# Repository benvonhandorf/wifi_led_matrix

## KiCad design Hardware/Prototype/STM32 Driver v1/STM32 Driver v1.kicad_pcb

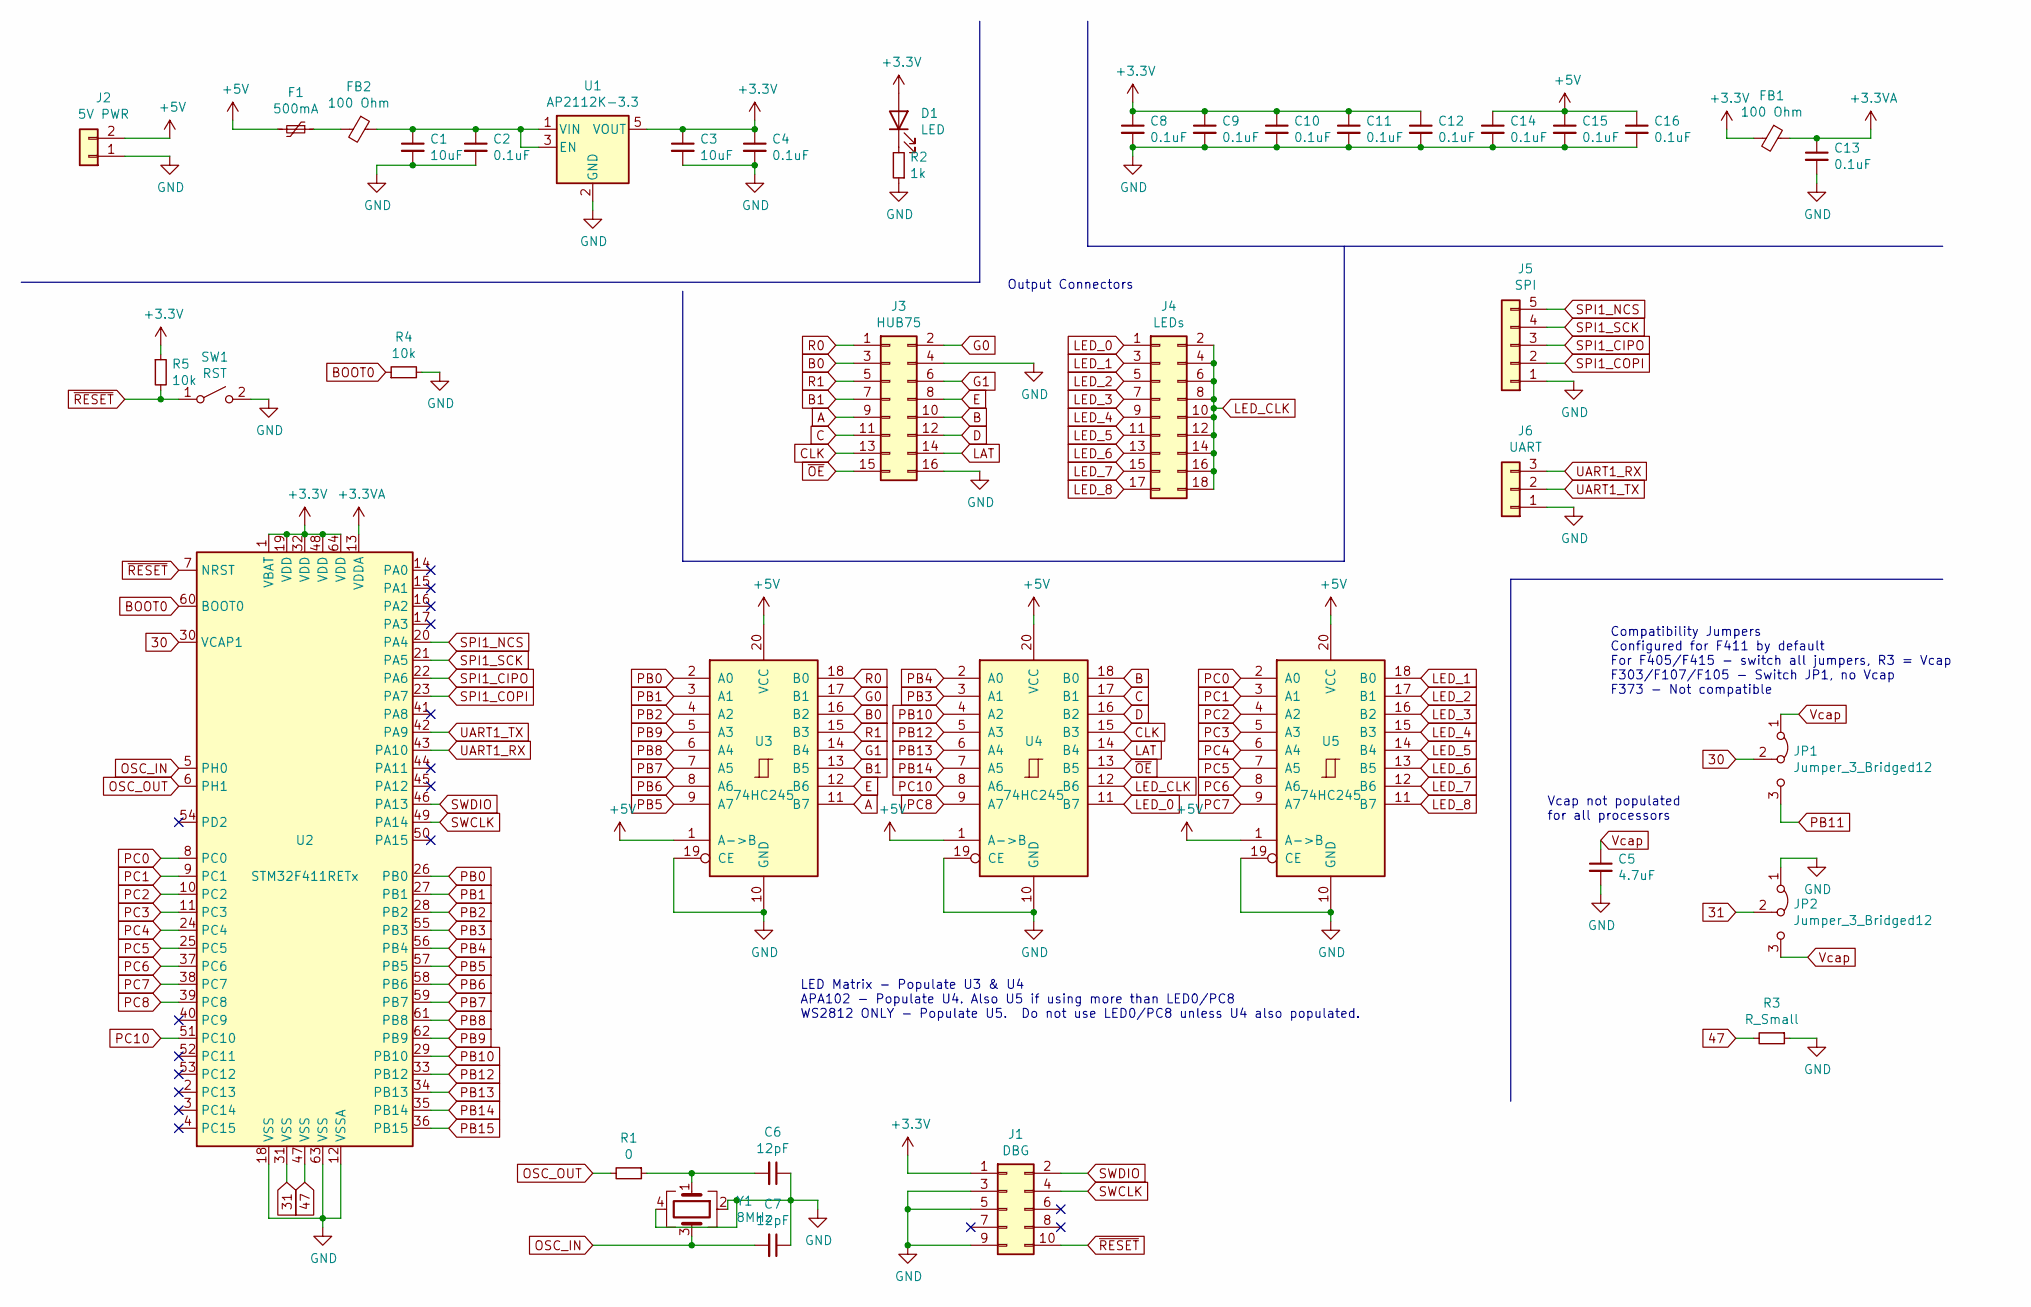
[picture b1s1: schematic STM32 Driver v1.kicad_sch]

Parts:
C1, C3: 10uF; C_0805_2012Metric
C2, C4, C8, C9, C10, C11, C12, C13, C14, C15, C16: 0.1uF; C_0603_1608Metric
C5: 4.7uF; C_0805_2012Metric
C6, C7: 12pF; C_0805_2012Metric
D1: LED; LED_0805_2012Metric
F1: 500mA; Fuse_1210_3225Metric
FB1, FB2: 100 Ohm; L_0805_2012Metric
J1: DBG; Cortex_Debug_PinSocket_2x05_P1.27mm_Vertical_SMD
J2: 5V PWR; TerminalBlock_Phoenix_MKDS-1,5-2-5.08_1x02_P5.08mm_Horizont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
J3: HUB75; IDC-Header_2x08_P2.54mm_Vertical
J4: LEDs; PinHeader_2x09_P2.54mm_Horizontal
J5: SPI; PinHeader_1x05_P2.54mm_Vertical
J6: UART; PinHeader_1x03_P2.54mm_Vertical
JP1, JP2: Jumper_3_Bridged12; SolderJumper-3_P1.3mm_Bridged12_Pad1.0x1.5mm
R1: 0; R_0603_1608Metric
R2: 1k; R_0805_2012Metric
R3: R_Small; R_0805_2012Metric_Pad1.15x1.40mm_HandSolder
R4, R5: 10k; R_0805_2012Metric
SW1: RST; Tac_SMD_6.4mm_Side_SPST_NO
U1: AP2112K-3.3; SOT-23-5
U2: STM32F411RETx; LQFP-64_10x10mm_P0.5mm
U3, U4, U5: 74HC245; TSSOP-20_4.4x6.5mm_P0.65mm
Y1: 8MHz; Crystal_SMD_5032-4Pin_5.0x3.2mm

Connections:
30: JP1.2 (C), U2.30 (VCAP1)
31: JP2.2 (C), U2.31 (VSS)
47: R3.2, U2.47 (VSS)
+3.3VA: C13.1, FB1.1, U2.13 (VDDA)
+5V: C14.1, C15.1, C16.1, F1.2, J2.2, U3.1 (A->B), U3.20 (VCC), U4.1 (A->B), U4.20 (VCC), U5.1 (A->B), U5.20 (VCC)
A: J3.9, U3.11 (B7)
B: J3.10, U4.18 (B0)
B0: J3.3, U3.16 (B2)
B1: J3.7, U3.13 (B5)
BOOT0: R4.1, U2.60 (BOOT0)
C: J3.11, U4.17 (B1)
CLK: J3.13, U4.15 (B3)
D: J3.12, U4.16 (B2)
E: J3.8, U3.12 (B6)
G0: J3.2, U3.17 (B1)
G1: J3.6, U3.14 (B4)
GND: C1.2, C2.2, C3.2, C4.2, C5.2, C6.1, C7.1, C8.2, C9.2, C10.2, C11.2, C12.2, C13.2, C14.2, C15.2, C16.2, J1.3, J1.5, J1.9, J2.1, J3.4, J3.16, J5.1, J6.1, JP2.1 (A), R2.1, R3.1, R4.2, SW1.2 (B), U1.2 (GND), U2.12 (VSSA), U2.18 (VSS), U2.63 (VSS), U3.10 (GND), U3.19 (CE), U4.10 (GND), U4.19 (CE), U5.10 (GND), U5.19 (CE), Y1.2, Y1.4
LAT: J3.14, U4.14 (B4)
LED_0: J4.1, U4.11 (B7)
LED_1: J4.3, U5.18 (B0)
LED_2: J4.5, U5.17 (B1)
LED_3: J4.7, U5.16 (B2)
LED_4: J4.9, U5.15 (B3)
LED_5: J4.11, U5.14 (B4)
LED_6: J4.13, U5.13 (B5)
LED_7: J4.15, U5.12 (B6)
LED_8: J4.17, U5.11 (B7)
LED_CLK: J4.2, J4.4, J4.6, J4.8, J4.10, J4.12, J4.14, J4.16, J4.18, U4.12 (B6)
unnamed: C1.1, C2.1, FB2.1, U1.1 (VIN), U1.3 (EN)
unnamed: C6.2, R1.1, Y1.1
unnamed: D1.1 (K), R2.2
unnamed: F1.1, FB2.2
OSC_IN: C7.2, U2.5 (PH0), Y1.3
OSC_OUT: R1.2, U2.6 (PH1)
PB0: U2.26 (PB0), U3.2 (A0)
PB1: U2.27 (PB1), U3.3 (A1)
PB2: U2.28 (PB2), U3.4 (A2)
PB3: U2.55 (PB3), U4.3 (A1)
PB4: U2.56 (PB4), U4.2 (A0)
PB5: U2.57 (PB5), U3.9 (A7)
PB6: U2.58 (PB6), U3.8 (A6)
PB7: U2.59 (PB7), U3.7 (A5)
PB8: U2.61 (PB8), U3.6 (A4)
PB9: U2.62 (PB9), U3.5 (A3)
PB10: U2.29 (PB10), U4.4 (A2)
PB11: JP1.3 (B)
PB12: U2.33 (PB12), U4.5 (A3)
PB13: U2.34 (PB13), U4.6 (A4)
PB14: U2.35 (PB14), U4.7 (A5)
PB15: U2.36 (PB15)
PC0: U2.8 (PC0), U5.2 (A0)
PC1: U2.9 (PC1), U5.3 (A1)
PC2: U2.10 (PC2), U5.4 (A2)
PC3: U2.11 (PC3), U5.5 (A3)
PC4: U2.24 (PC4), U5.6 (A4)
PC5: U2.25 (PC5), U5.7 (A5)
PC6: U2.37 (PC6), U5.8 (A6)
PC7: U2.38 (PC7), U5.9 (A7)
PC8: U2.39 (PC8), U4.9 (A7)
PC10: U2.51 (PC10), U4.8 (A6)
R0: J3.1, U3.18 (B0)
R1: J3.5, U3.15 (B3)
SPI1_CIPO: J5.3, U2.22 (PA6)
SPI1_COPI: J5.2, U2.23 (PA7)
SPI1_NCS: J5.5, U2.20 (PA4)
SPI1_SCK: J5.4, U2.21 (PA5)
SWCLK: J1.4, U2.49 (PA14)
SWDIO: J1.2, U2.46 (PA13)
UART1_RX: J6.3, U2.43 (PA10)
UART1_TX: J6.2, U2.42 (PA9)
Vcap: C5.1, JP1.1 (A), JP2.3 (B)
~OE: J3.15, U4.13 (B5)
~RESET: J1.10, R5.2, SW1.1 (A), U2.7 (NRST)

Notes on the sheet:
Vcap not populated for all processors
Output Connectors
LED Matrix - Populate U3 & U4 APA102 - Populate U4. Also U5 if using more than LED0/PC8 WS2812 ONLY - Populate U5. Do not use LED0/PC8 unless U4 also populated.
Compatibility Jumpers Configured for F411 by default For F405/F415 - switch all jumpers, R3 = Vcap F303/F107/F105 - Switch JP1, no Vcap F373 - Not compatible

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
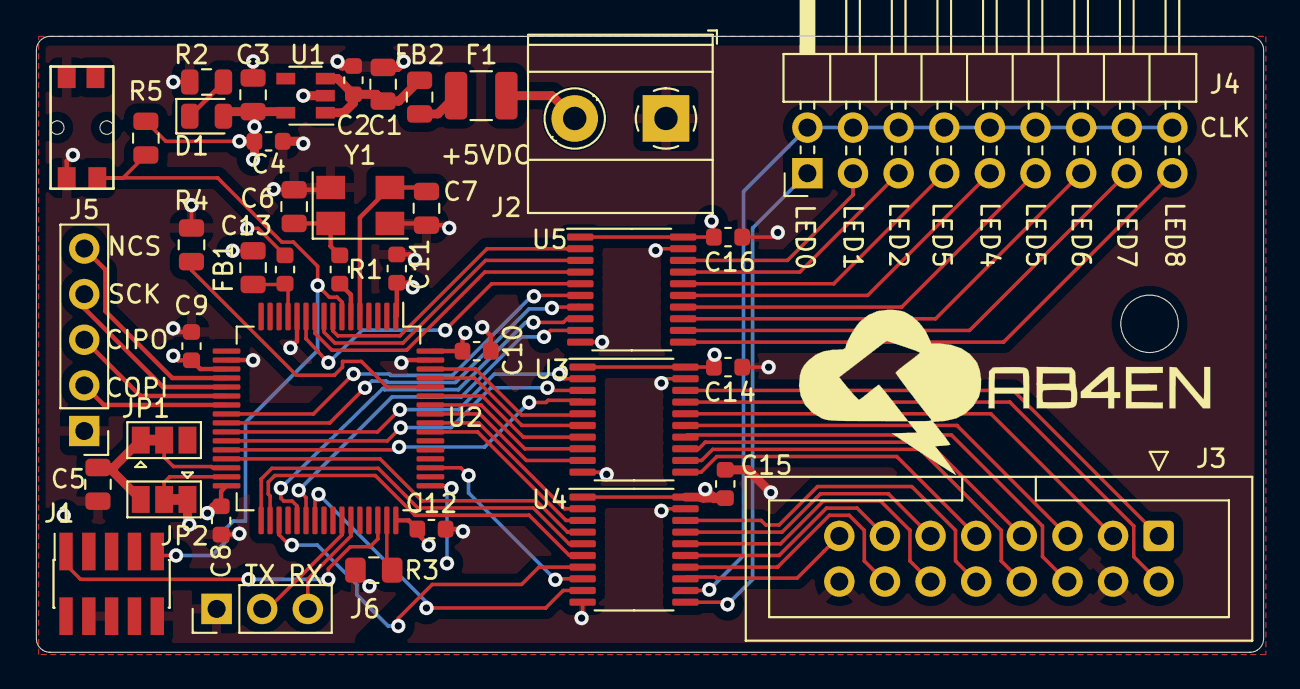
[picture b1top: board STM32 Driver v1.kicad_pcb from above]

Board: 4 copper layers, 68.3 x 34.3 mm, 40 parts (0 on the bottom side), 72 nets.

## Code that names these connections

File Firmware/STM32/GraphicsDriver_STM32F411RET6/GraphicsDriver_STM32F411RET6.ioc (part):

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Mcu.Name=STM32F411R(C-E)Tx
Mcu.Package=LQFP64
Mcu.UserName=STM32F411RETx
PA10.Mode=Asynchronous
PA10.Signal=USART1_RX
PA13.Mode=Serial_Wire
PA13.Signal=SYS_JTMS-SWDIO
PA14.Mode=Serial_Wire
PA14.Signal=SYS_JTCK-SWCLK
PA4.GPIOParameters=GPIO_PuPd,GPIO_Label,GPIO_ModeDefaultEXTI
PA4.GPIO_Label=SPI1_NCS
PA4.GPIO_ModeDefaultEXTI=GPIO_MODE_IT_RISING
PA4.GPIO_PuPd=GPIO_PULLUP
PA4.Signal=GPXTI4
PA5.Mode=Full_Duplex_Slave
PA5.Signal=SPI1_SCK
PA6.Mode=Full_Duplex_Slave
PA6.Signal=SPI1_MISO
PA7.Mode=Full_Duplex_Slave
PA7.Signal=SPI1_MOSI
PA9.Mode=Asynchronous
PA9.Signal=USART1_TX
PB0.GPIOParameters=GPIO_Label
PB0.GPIO_Label=Matrix_R0
PB0.Signal=GPIO_Output
PB1.GPIOParameters=GPIO_Label
PB1.GPIO_Label=Matrix_G0
PB1.Signal=GPIO_Output
PB10.GPIOParameters=GPIO_Label
PB10.GPIO_Label=Matrix_D
PB10.Signal=GPIO_Output
PB12.GPIOParameters=GPIO_Label
PB12.GPIO_Label=Matrix_CLK
PB12.Signal=GPIO_Output
PB13.GPIOParameters=GPIO_Label
PB13.GPIO_Label=Matrix_LAT
PB13.Signal=GPIO_Output
PB14.GPIOParameters=GPIO_Label
PB14.GPIO_Label=Matrix_OE
PB14.Signal=GPIO_Output
PB2.GPIOParameters=GPIO_Label
PB2.GPIO_Label=Matrix_B0
PB2.Signal=GPIO_Output
PB3.GPIOParameters=GPIO_Label
PB3.GPIO_Label=Matrix_C
PB3.Signal=GPIO_Output
PB4.GPIOParameters=GPIO_Label
PB4.GPIO_Label=Matrix_B
PB4.Signal=GPIO_Output
PB5.GPIOParameters=GPIO_Label
PB5.GPIO_Label=Matrix_A
PB5.Signal=GPIO_Output
PB6.GPIOParameters=GPIO_Label
PB6.GPIO_Label=Matrix_E
PB6.Signal=GPIO_Output
PB7.GPIOParameters=GPIO_Label
PB7.GPIO_Label=Matrix_B1
PB7.Signal=GPIO_Output
PB8.GPIOParameters=GPIO_Label
PB8.GPIO_Label=Matrix_G1
PB8.Signal=GPIO_Output
PB9.GPIOParameters=GPIO_Label
PB9.GPIO_Label=Matrix_R1
PB9.Signal=GPIO_Output
PC0.GPIOParameters=GPIO_Label
PC0.GPIO_Label=LED_1
PC0.Signal=GPIO_Output
PC1.GPIOParameters=GPIO_Label
PC1.GPIO_Label=LED_2
PC1.Signal=GPIO_Output
PC10.GPIOParameters=GPIO_Label
PC10.GPIO_Label=LED_CLK
PC10.Signal=GPIO_Output
PC2.GPIOParameters=GPIO_Label
PC2.GPIO_Label=LED_3
PC2.Signal=GPIO_Output
PC3.GPIOParameters=GPIO_Label
PC3.GPIO_Label=LED_4
PC3.Signal=GPIO_Output
PC4.GPIOParameters=GPIO_Label
PC4.GPIO_Label=LED_5
PC4.Signal=GPIO_Output
PC5.GPIOParameters=GPIO_Label
PC5.GPIO_Label=LED_6
PC5.Signal=GPIO_Output
PC6.GPIOParameters=GPIO_Label
PC6.GPIO_Label=LED_7
PC6.Signal=GPIO_Output
PC7.GPIOParameters=GPIO_Label
PC7.GPIO_Label=LED_8
PC7.Signal=GPIO_Output
PC8.GPIOParameters=GPIO_Label
PC8.GPIO_Label=LED_0
PC8.Signal=GPIO_Output
PH0\ -\ OSC_IN.Mode=HSE-External-Oscillator
PH0\ -\ OSC_IN.Signal=RCC_OSC_IN
PH1\ -\ OSC_OUT.Mode=HSE-External-Oscillator
PH1\ -\ OSC_OUT.Signal=RCC_OSC_OUT
RCC.HSE_VALUE=8000000
RCC.SYSCLKFreq_VALUE=100000000
RCC.SYSCLKSource=RCC_SYSCLKSOURCE_PLLCLK
board=custom

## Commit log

2020-09-26 Basic gif-frames library working
2020-10-11 Basic matrix comms
2020-10-11 Fix overrun, implement IWDG
2020-10-12 Clock configuration - Pre-DMA work
2020-10-13 WIP on DMA
2020-10-18 WIP DMA tuning
2020-10-19 TIM2 triggered by TIM3 - Sort of works
2020-10-21 DMA pixel clocking
2020-10-21 Fixed OE timing, support easily switch able test modes, basic image processing script
2020-10-21 WIP - pin remapping
2020-10-22 Before plane refactor
2020-10-22 Planes implemented but having pixel bleed issues
2020-10-22 BCM timing tweaks and LUT.
2020-10-25 WIP on converting to a single port output always using DMA
2020-10-25 Remove prescalar
2020-10-26 Big buffer DMA working
2020-11-12 Before multi-board refactor
2020-11-13 Refactor to use Cube pin assignments from project
2020-11-13 WIP - F411 port - Compiling but corrupted
2020-11-13 WIP debugging F411 crash
2020-11-15 Fix ridiculous math bug
2020-11-15 WIP Debugging image mode
2020-11-15 Dithering function work
2020-11-17 Gamma correction
2020-11-22 Configuration support and display interface refactor
2020-11-24 Multi-frame image support
2020-12-09 Network comms
2020-12-16 Command processor and network WIP
2020-12-19 Library projects compiled and working on MCU
2020-12-20 Fix for LedSingleWire driver initialization
2020-12-23 Cross MCU communication working with large gaps
2020-12-27 Working at ~6MHz
2020-12-29 Multiple particle support, new commands for clearing and assigning sparse pixels
2020-12-29 Random race
2021-01-12 STM32F411RE Board Bringup complete
2021-01-16 Before SPI speed debugging
2021-01-18 Matrix communication operational with excessive delays
2021-01-24 Reconfiguration support
2021-03-01 FFT working on I2S data
2021-03-08 Display and control refactor
2021-04-06 Fix for wifi connectivity and initial HTTP server work
2021-04-17 Move I2S to pin 17 for compatibility with M5Cube
2021-04-17 Fix component fiasco
2021-04-17 Finally compiling
2021-04-18 M5 Display WIP
2021-10-05 Add package.json
2023-02-08 Rebuild WIP
2023-02-08 First CMake based build end to end
2023-03-03 VSCode compilation of ES32 and STM32 code
2023-03-05 Wifi connection issue resolved (?)
